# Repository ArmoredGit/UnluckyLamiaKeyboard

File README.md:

# UnluckyLamiaKeyboard
Every file needed to reproduce my custom 54% keyboard, which I've named Unlucky Lamia.

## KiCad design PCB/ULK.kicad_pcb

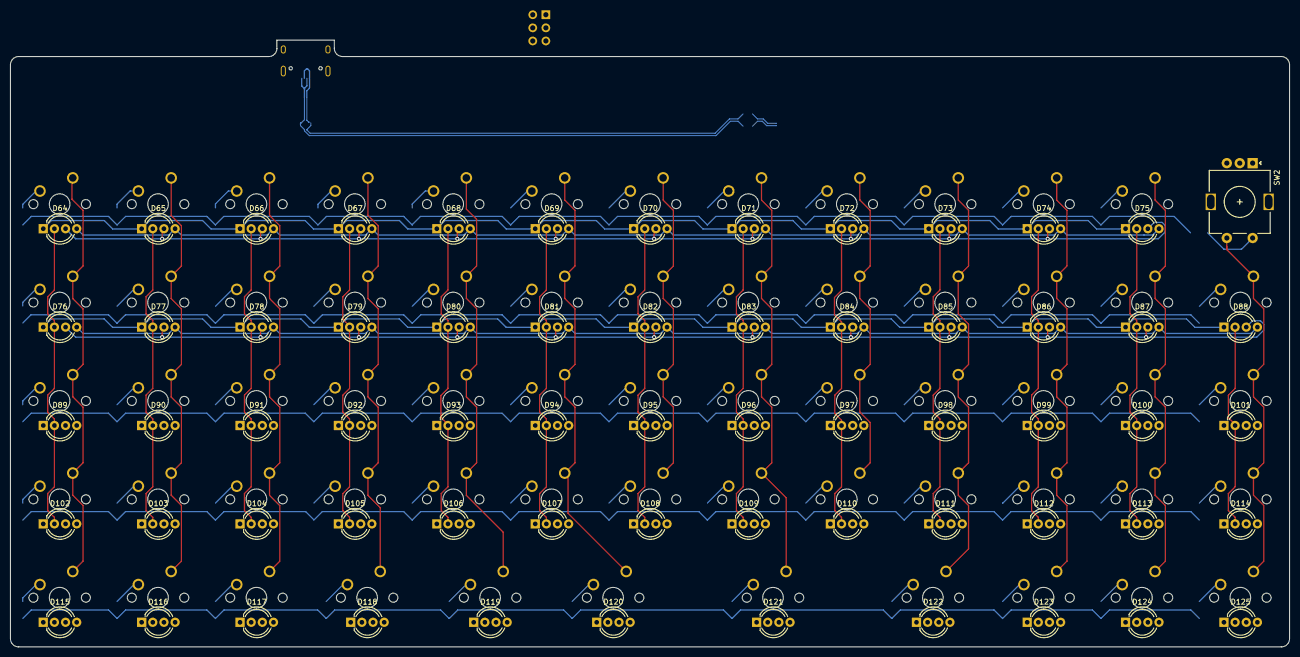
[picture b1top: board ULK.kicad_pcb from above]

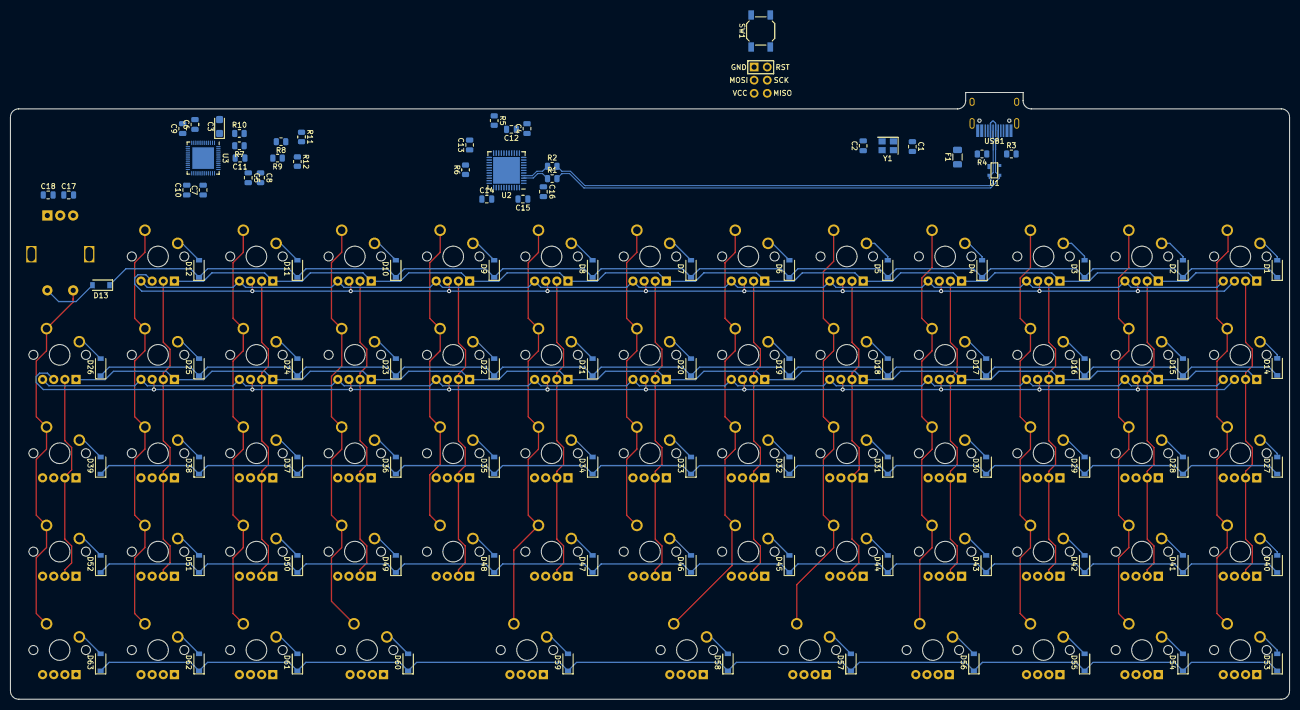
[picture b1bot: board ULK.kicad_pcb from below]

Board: 2 copper layers, 247.6 x 117.5 mm, 226 parts (101 on the bottom side), 133 nets.

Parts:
C1, C2: 22p; C_0805_2012Metric
C3: 22uF/10V; CP_EIA-3216-18_Kemet-A
C4: 1u; C_0805_2012Metric
C5, C6, C7, C11: 0.47u; C_0805_2012Metric
C8, C9, C10, C12, C13, C14, C15: 0.1u; C_0805_2012Metric
C16: 10u; C_0805_2012Metric
C17, C18: 100nf; C_0805_2012Metric
D1, D2, D3, D4, D5, D6, D7, D8, D9, D10, D11, D12, D13, D14, D15, D16, D17, D18, D19, D20, D21, D22, D23, D24, D25, D26, D27, D28, D29, D30, D31, D32, D33, D34, D35, D36, D37, D38, D39, D40, D41, D42, D43, D44, D45, D46, D47, D48, D49, D50, D51, D52, D53, D54, D55, D56, D57, D58, D59, D60, D61, D62, D63: D; D_SOD-123
D64, D65, D66, D67, D68, D69, D70, D71, D72, D73, D74, D75, D76, D77, D78, D79, D80, D81, D82, D83, D84, D85, D86, D87, D88, D89, D90, D91, D92, D93, D94, D95, D96, D97, D98, D99, D100, D101, D102, D103, D104, D105, D106, D107, D108, D109, D110, D111, D112, D113, D114, D115, D116, D117, D118, D119, D120, D121, D122, D123, D124, D125: LED_RAGB; LED_D5.0mm-4_RGB_Wide_Pins
F1: 500m; Fuse_1206_3216Metric
J1: AVR-ISP-6; Reset_Pretty-Mask
K1, K2, K3, K4, K5, K6, K7, K8, K9, K10, K11, K12, K13, K14, K15, K16, K17, K18, K19, K20, K21, K22, K23, K24, K25, K26, K27, K28, K29, K30, K31, K32, K33, K34, K35, K36, K37, K38, K39, K40, K41, K42, K43, K44, K45, K46, K47, K48, K49, K50, K51, K52, K53, K54, K58, K60, K61, K62: SW_Push; MXOnly-1U-NoLED
K55, K56, K57, K59: SW_Push; MXOnly-1.25U-NoLED
R1, R2: 22; R_0805_2012Metric
R3, R4: 5.1k; R_0805_2012Metric
R5, R6: 10k; R_0805_2012Metric
R7, R10, R11: 100k; R_0805_2012Metric
R8, R9: 2k; R_0805_2012Metric
R12: 20k; R_0805_2012Metric
SW1: SW_Push; SW_SPST_SKQG_WithStem
SW2: Rotary_Encoder_Switch; RotaryEncoder_Alps_EC11E-Switch_Vertical_H20mm
U1: PRTR5V0U2X; SOT143B
U2: ATmega32U4-MU; QFN-44-1EP_7x7mm_P0.5mm_EP5.2x5.2mm
U3: IS31FL3733-QF; QFN-48-1EP_6x6mm_P0.4mm_EP4.2x4.2mm
USB1: HRO-TYPE-C-31-M-12; HRO-TYPE-C-31-M-12-HandSoldering
Y1: XTAL; Crystal_SMD_3225-4Pin_3.2x2.5mm

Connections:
+5V: C3.1, C5.2, C6.2, C7.2, C8.2, C9.2, C10.2, C12.1, C13.1, C14.1, C15.1, C16.1, F1.1, J1.2, R5.1, U2.2, U2.7, U2.14, U2.24, U2.34, U2.44, U3.20, U3.29, U3.37, U3.38
CS1: D64.2, D76.2, D89.2, D102.2, U3.16
CS2: D65.2, D77.2, D90.2, D103.2, U3.17
CS3: D66.2, D78.2, D91.2, D104.2, U3.18
CS4: D67.2, D79.2, D92.2, D105.2, U3.19
CS5: D68.2, D80.2, D93.2, D106.2, U3.21
CS6: D69.2, D81.2, D94.2, D107.2, U3.22
CS7: D70.2, D82.2, D95.2, D108.2, U3.23
CS8: D71.2, D83.2, D96.2, D109.2, U3.24
CS9: D72.2, D84.2, D97.2, D110.2, U3.25
CS10: D73.2, D85.2, D98.2, D111.2, U3.26
CS11: D74.2, D86.2, D99.2, D112.2, U3.27
CS12: D75.2, D87.2, D100.2, D113.2, U3.28
CS13: D88.2, D101.2, D114.2, U3.30
CS14: D115.2, D118.2, D121.2, D124.2, U3.31
CS15: D116.2, D119.2, D122.2, D125.2, U3.32
CS16: D117.2, D120.2, D123.2, U3.33
Col0: K1.2, K13.2, K26.2, K39.2, K52.2, U2.20
Col1: K2.2, K14.2, K27.2, K40.2, K53.2, U2.21
Col2: K3.2, K15.2, K28.2, K41.2, K54.2, U2.25
Col3: K4.2, K16.2, K29.2, K42.2, K55.2, U2.22
Col4: K5.2, K17.2, K30.2, K43.2, K56.2, U2.26
Col5: K6.2, K18.2, K31.2, K44.2, K57.2, U2.27
Col6: K7.2, K19.2, K32.2, K45.2, U2.36
Col7: K8.2, K20.2, K33.2, K46.2, K58.2, U2.37
Col8: K9.2, K21.2, K34.2, K47.2, U2.38
Col9: K10.2, K22.2, K35.2, K48.2, K59.2, U2.39
Col10: K11.2, K23.2, K36.2, K49.2, K60.2, U2.40
Col11: K12.2, K24.2, K37.2, K50.2, K61.2, U2.41
Col12: K25.2, K38.2, K51.2, K62.2, SW2.S1, U2.1
D+: R2.1, U2.4
D-: R1.1, U2.3
DN: R1.2, U1.3, USB1.5, USB1.7
DP: R2.2, U1.2, USB1.6, USB1.8
GND: C1.2, C2.2, C3.2, C4.2, C5.1, C6.1, C7.1, C8.1, C9.1, C10.1, C11.1, C12.2, C13.2, C14.2, C15.2, C16.2, C17.1, C18.2, J1.6, R3.2, R4.2, R6.1, R10.2, R11.2, R12.2, SW1.1, SW2.C, U1.1, U2.5, U2.15, U2.23, U2.35, U2.43, U2.45, U3.5, U3.12, U3.34, U3.43, U3.44, U3.48, U3.49, USB1.1, USB1.12, USB1.13, Y1.2, Y1.4
MISO: J1.1, U2.11
MOSI: J1.4, U2.10
unnamed: C4.1, U2.6
unnamed: D1.2, K1.1
unnamed: D2.2, K2.1
unnamed: D3.2, K3.1
unnamed: D4.2, K4.1
unnamed: D5.2, K5.1
unnamed: D6.2, K6.1
unnamed: D7.2, K7.1
unnamed: D8.2, K8.1
unnamed: D9.2, K9.1
unnamed: D10.2, K10.1
unnamed: D11.2, K11.1
unnamed: D12.2, K12.1
unnamed: D13.2, SW2.S2
unnamed: D14.2, K13.1
unnamed: D15.2, K14.1
unnamed: D16.2, K15.1
unnamed: D17.2, K16.1
unnamed: D18.2, K17.1
unnamed: D19.2, K18.1
unnamed: D20.2, K19.1
unnamed: D21.2, K20.1
unnamed: D22.2, K21.1
unnamed: D23.2, K22.1
unnamed: D24.2, K23.1
unnamed: D25.2, K24.1
unnamed: D26.2, K25.1
unnamed: D27.2, K26.1
unnamed: D28.2, K27.1
unnamed: D29.2, K28.1
unnamed: D30.2, K29.1
unnamed: D31.2, K30.1
unnamed: D32.2, K31.1
unnamed: D33.2, K32.1
unnamed: D34.2, K33.1
unnamed: D35.2, K34.1
unnamed: D36.2, K35.1
unnamed: D37.2, K36.1
unnamed: D38.2, K37.1
unnamed: D39.2, K38.1
unnamed: D40.2, K39.1
unnamed: D41.2, K40.1
unnamed: D42.2, K41.1
unnamed: D43.2, K42.1
unnamed: D44.2, K43.1
unnamed: D45.2, K44.1
unnamed: D46.2, K45.1
unnamed: D47.2, K46.1
unnamed: D48.2, K47.1
unnamed: D49.2, K48.1
unnamed: D50.2, K49.1
unnamed: D51.2, K50.1
unnamed: D52.2, K51.1
unnamed: D53.2, K52.1
unnamed: D54.2, K53.1
unnamed: D55.2, K54.1
unnamed: D56.2, K55.1
unnamed: D57.2, K56.1
unnamed: D58.2, K57.1
unnamed: D59.2, K58.1
unnamed: D60.2, K59.1
unnamed: D61.2, K60.1
unnamed: D62.2, K61.1
unnamed: D63.2, K62.1
unnamed: R3.1, USB1.10
unnamed: R4.1, USB1.4
unnamed: R6.2, U2.33
unnamed: R7.2, U3.45
unnamed: R11.1, U3.47
unnamed: R12.1, U3.35
RESET: J1.5, R5.2, SW1.2, U2.13
Rot0: C18.1, SW2.A, U2.12
Rot1: C17.2, SW2.B, U2.8
Row0: D1.1, D2.1, D3.1, D4.1, D5.1, D6.1, D7.1, D8.1, D9.1, D10.1, D11.1, D12.1, D13.1, U2.28
Row1: D14.1, D15.1, D16.1, D17.1, D18.1, D19.1, D20.1, D21.1, D22.1, D23.1, D24.1, D25.1, D26.1, U2.29
Row2: D27.1, D28.1, D29.1, D30.1, D31.1, D32.1, D33.1, D34.1, D35.1, D36.1, D37.1, D38.1, D39.1, U2.30
Row3: D40.1, D41.1, D42.1, D43.1, D44.1, D45.1, D46.1, D47.1, D48.1, D49.1, D50.1, D51.1, D52.1, U2.31
Row4: D53.1, D54.1, D55.1, D56.1, D57.1, D58.1, D59.1, D60.1, D61.1, D62.1, D63.1, U2.32
SCK: J1.3, U2.9
SCL: R8.2, U2.18, U3.42
SDA: R9.2, U2.19, U3.41
SW1: D102.4, D103.4, D104.4, D105.4, D106.4, D107.4, D108.4, D109.4, D110.4, D111.4, D112.4, D113.4, D114.4, D115.4, D116.4, D117.4, U3.2
SW2: D102.3, D103.3, D104.3, D105.3, D106.3, D107.3, D108.3, D109.3, D110.3, D111.3, D112.3, D113.3, D114.3, D115.3, D116.3, D117.3, U3.3
SW3: D102.1, D103.1, D104.1, D105.1, D106.1, D107.1, D108.1, D109.1, D110.1, D111.1, D112.1, D113.1, D114.1, D115.1, D117.1, U3.4
SW4: D89.4, D90.4, D91.4, D92.4, D93.4, D94.4, D95.4, D96.4, D97.4, D98.4, D99.4, D100.4, D101.4, D118.4, D119.4, D120.4, U3.6
SW5: D89.3, D90.3, D91.3, D92.3, D93.3, D94.3, D95.3, D96.3, D97.3, D98.3, D99.3, D100.3, D101.3, D118.3, D119.3, D120.3, U3.7
SW6: D89.1, D90.1, D91.1, D92.1, D93.1, D94.1, D95.1, D96.1, D97.1, D98.1, D99.1, D100.1, D101.1, D118.1, D119.1, D120.1, U3.8
SW7: D76.4, D77.4, D78.4, D79.4, D80.4, D81.4, D82.4, D83.4, D84.4, D85.4, D86.4, D87.4, D88.4, D121.4, D122.4, D123.4, U3.9
SW8: D76.3, D77.3, D78.3, D79.3, D80.3, D81.3, D82.3, D83.3, D84.3, D85.3, D86.3, D87.3, D88.3, D121.3, D122.3, D123.3, U3.10
SW9: D76.1, D77.1, D78.1, D79.1, D80.1, D81.1, D82.1, D83.1, D84.1, D85.1, D86.1, D87.1, D88.1, D121.1, D122.1, D123.1, U3.11
SW10: D64.4, D65.4, D66.4, D67.4, D68.4, D69.4, D70.4, D71.4, D72.4, D73.4, D74.4, D75.4, D124.4, D125.4, U3.13
SW11: D64.3, D65.3, D66.3, D67.3, D68.3, D69.3, D70.3, D71.3, D72.3, D73.3, D74.3, D75.3, D124.3, D125.3, U3.14
SW12: D64.1, D65.1, D66.1, D67.1, D68.1, D69.1, D70.1, D71.1, D72.1, D73.1, D74.1, D75.1, D124.1, D125.1, U3.15
VCC: C11.2, F1.2, R7.1, R8.1, R9.1, R10.1, U1.4, U3.39, U3.46, USB1.2, USB1.11
XTAL1: C1.1, U2.17, Y1.1
XTAL2: C2.1, U2.16, Y1.3

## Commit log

2021-06-28 added image folder
2021-06-28 Image folder and layout
2021-06-28 adding details
2021-06-29 PCB and Midplate/case basics
2021-06-29 wiring schematic pdf
2021-06-29 Updates to the PCB
2021-06-30 PCB to the tracing stage
2021-06-30 beginning of ver 1.1
2021-07-03 Testing some venting for the back of the case
2021-07-09 updated case and midplate along with assembly
